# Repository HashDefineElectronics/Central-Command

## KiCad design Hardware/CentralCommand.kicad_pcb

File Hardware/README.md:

# Central-Command
The centralized board that will control the roll with it project

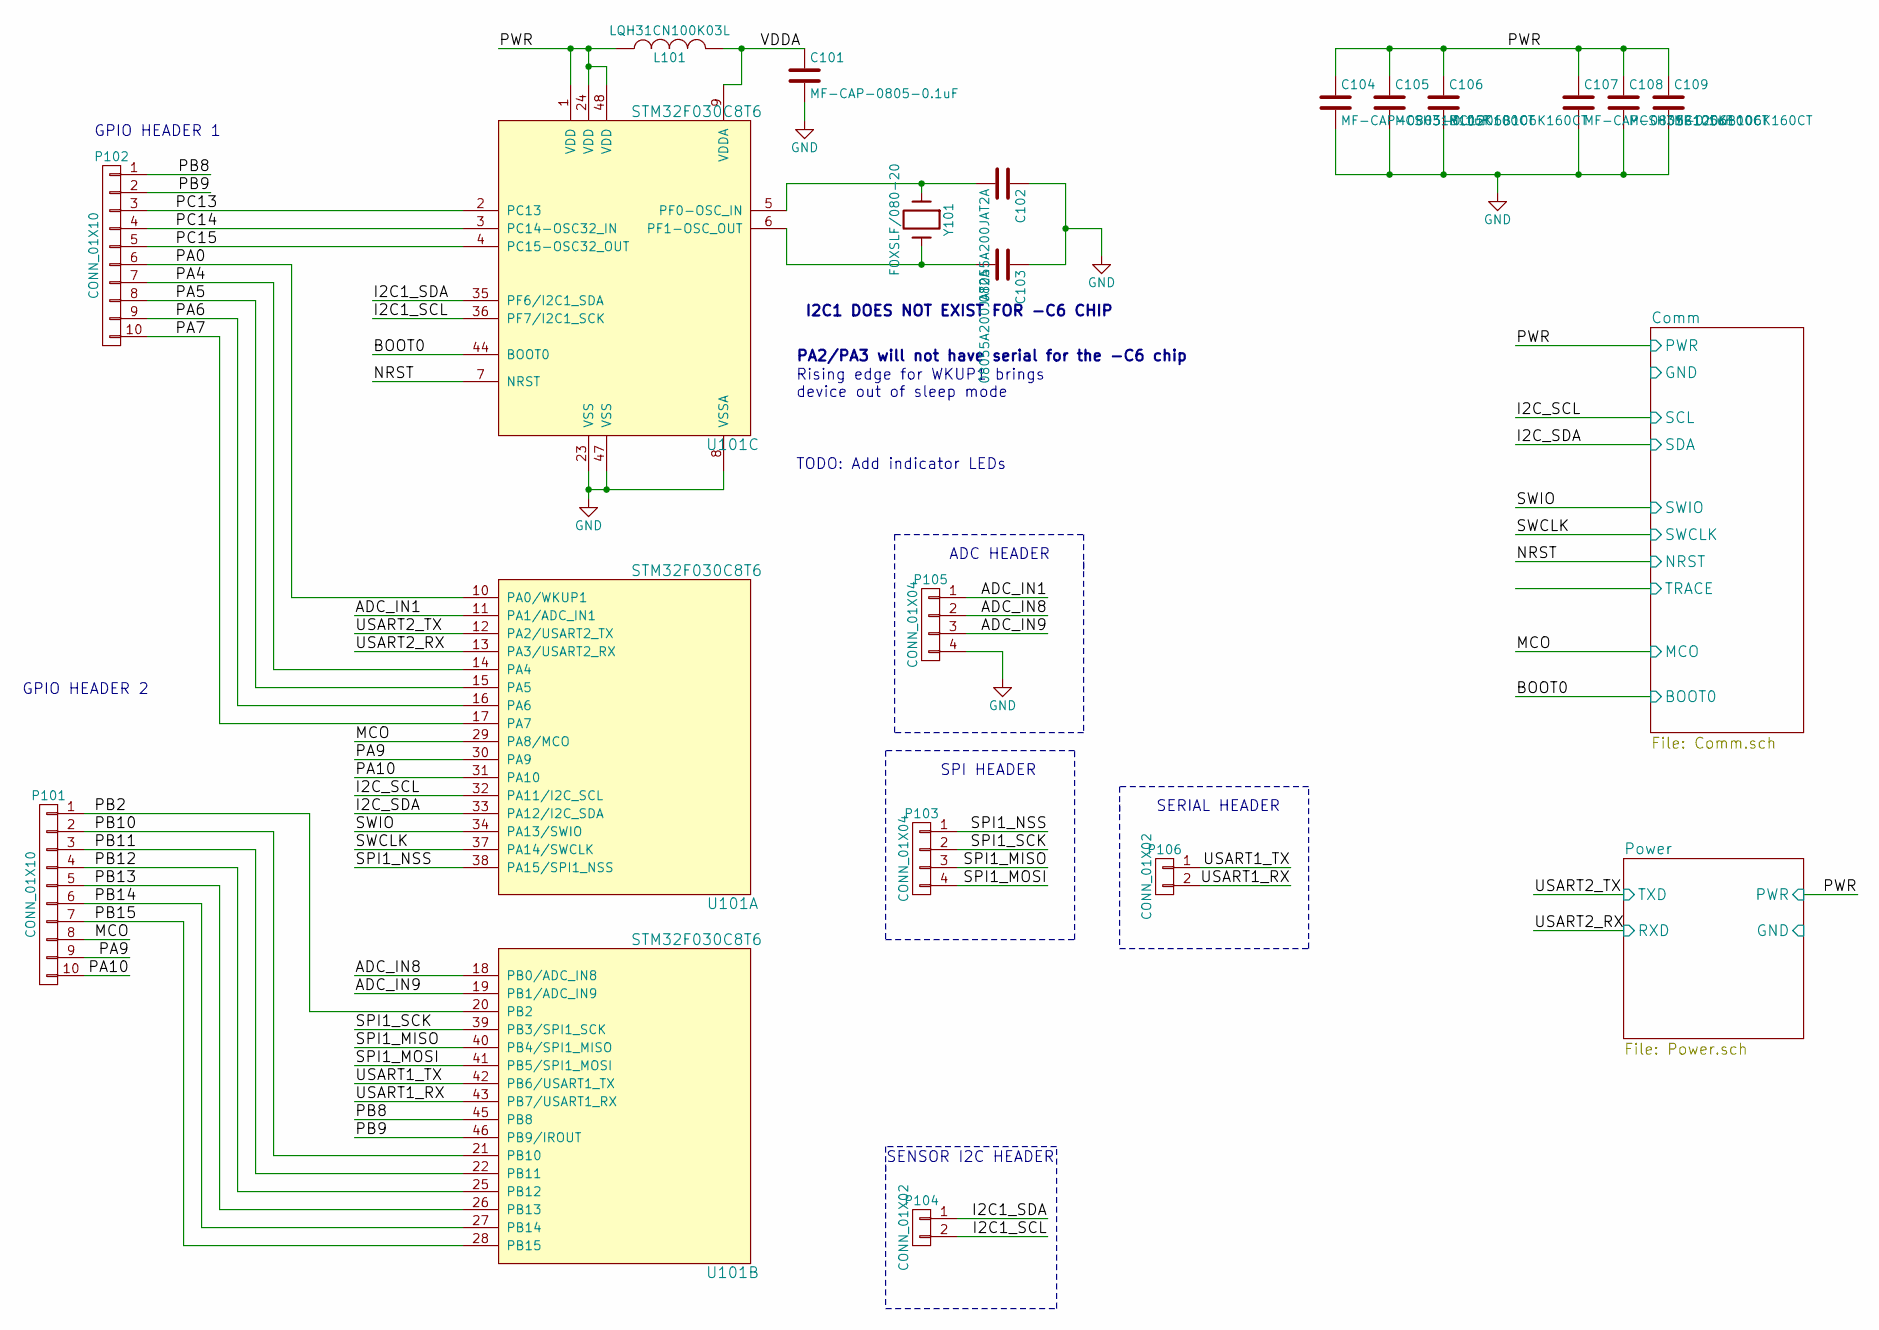
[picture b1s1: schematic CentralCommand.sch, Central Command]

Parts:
C101, C104, C107: MF-CAP-0805-0.1uF; C_0805; MPN 0805B104K500CT; Farnell 2496944
C102, C103: 08055A200JAT2A; C_0805; MPN 08055A200JAT2A; Farnell 2332762
C105, C108: MCSH31B105K100CT; C_1206; MPN MCSH31B105K100CT; Farnell 1856632
C106, C109: MC1206B106K160CT; C_1206; MPN MC1206B106K160CT; Farnell 2320921
L101: LQH31CN100K03L; Neosid_Inductor_SM1206; MPN LQH31CN100K03L; Farnell 1515399
P101, P102: CONN_01X10; Pin_Header_Straight_1x10; MPN M20-9991046; Farnell 1022261
P103, P105: CONN_01X04; Pin_Header_Straight_1x04; MPN M20-9990446; Farnell 1022251
P104, P106: CONN_01X02; Pin_Header_Straight_1x02; MPN M20-9990246; Farnell 1022247
U101: STM32F030C8T6; LQFP-48_7x7mm_Pitch0.5mm; MPN STM32F030C8; Farnell 2393634
Y101: FOXSLF/080-20; Crystal_HC49-U_Vertical; MPN FOXSLF/080-20; Farnell 2063945

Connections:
/ADC_IN1: P105.1, U101.11 (PA1/ADC_IN1)
/ADC_IN8: P105.2, U101.18 (PB0/ADC_IN8)
/ADC_IN9: P105.3, U101.19 (PB1/ADC_IN9)
/Comm/BOOT0: U101.44 (BOOT0); also elsewhere on the board
/Comm/NRST: U101.7 (NRST); also elsewhere on the board
/Comm/PWR: C104.1, C105.1, C106.1, C107.1, C108.1, C109.1, L101.1, U101.1 (VDD), U101.24 (VDD), U101.48 (VDD); also elsewhere on the board
/Comm/SCL: U101.32 (PA11/I2C_SCL); also elsewhere on the board
/Comm/SDA: U101.33 (PA12/I2C_SDA); also elsewhere on the board
/Comm/SWCLK: U101.37 (PA14/SWCLK); also elsewhere on the board
/Comm/SWIO: U101.34 (PA13/SWIO); also elsewhere on the board
/I2C1_SCL: P104.2, U101.36 (PF7/I2C1_SCK)
/I2C1_SDA: P104.1, U101.35 (PF6/I2C1_SDA)
/MCO: P101.8, U101.29 (PA8/MCO)
/PA0: P102.6, U101.10 (PA0/WKUP1)
/PA4: P102.7, U101.14 (PA4)
/PA5: P102.8, U101.15 (PA5)
/PA6: P102.9, U101.16 (PA6)
/PA7: P102.10, U101.17 (PA7)
/PA9: P101.9, U101.30 (PA9)
/PA10: P101.10, U101.31 (PA10)
/PB2: P101.1, U101.20 (PB2)
/PB8: P102.1, U101.45 (PB8)
/PB9: P102.2, U101.46 (PB9/IROUT)
/PB10: P101.2, U101.21 (PB10)
/PB11: P101.3, U101.22 (PB11)
/PB12: P101.4, U101.25 (PB12)
/PB13: P101.5, U101.26 (PB13)
/PB14: P101.6, U101.27 (PB14)
/PB15: P101.7, U101.28 (PB15)
/PC13: P102.3, U101.2 (PC13)
/PC14: P102.4, U101.3 (PC14-OSC32_IN)
/PC15: P102.5, U101.4 (PC15-OSC32_OUT)
/Power/RXD: U101.13 (PA3/USART2_RX); also elsewhere on the board
/Power/TXD: U101.12 (PA2/USART2_TX); also elsewhere on the board
/SPI1_MISO: P103.3, U101.40 (PB4/SPI1_MISO)
/SPI1_MOSI: P103.4, U101.41 (PB5/SPI1_MOSI)
/SPI1_NSS: P103.1, U101.38 (PA15/SPI1_NSS)
/SPI1_SCK: P103.2, U101.39 (PB3/SPI1_SCK)
/USART1_RX: P106.2, U101.43 (PB7/USART1_RX)
/USART1_TX: P106.1, U101.42 (PB6/USART1_TX)
/VDDA: C101.1, L101.2, U101.9 (VDDA)
GND: C101.2, C102.1, C103.1, C104.2, C105.2, C106.2, C107.2, C108.2, C109.2, P105.4, U101.8 (VSSA), U101.23 (VSS), U101.47 (VSS); also elsewhere on the board
unnamed: C102.2, U101.5 (PF0-OSC_IN), Y101.1
unnamed: C103.2, U101.6 (PF1-OSC_OUT), Y101.2

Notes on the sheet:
I2C1 DOES NOT EXIST FOR -C6 CHIP
PA2/PA3 will not have serial for the -C6 chip
Rising edge for WKUP1 brings device out of sleep mode
GPIO HEADER 1
ADC HEADER
SPI HEADER
SERIAL HEADER
SENSOR I2C HEADER
GPIO HEADER 2
TODO: Add indicator LEDs

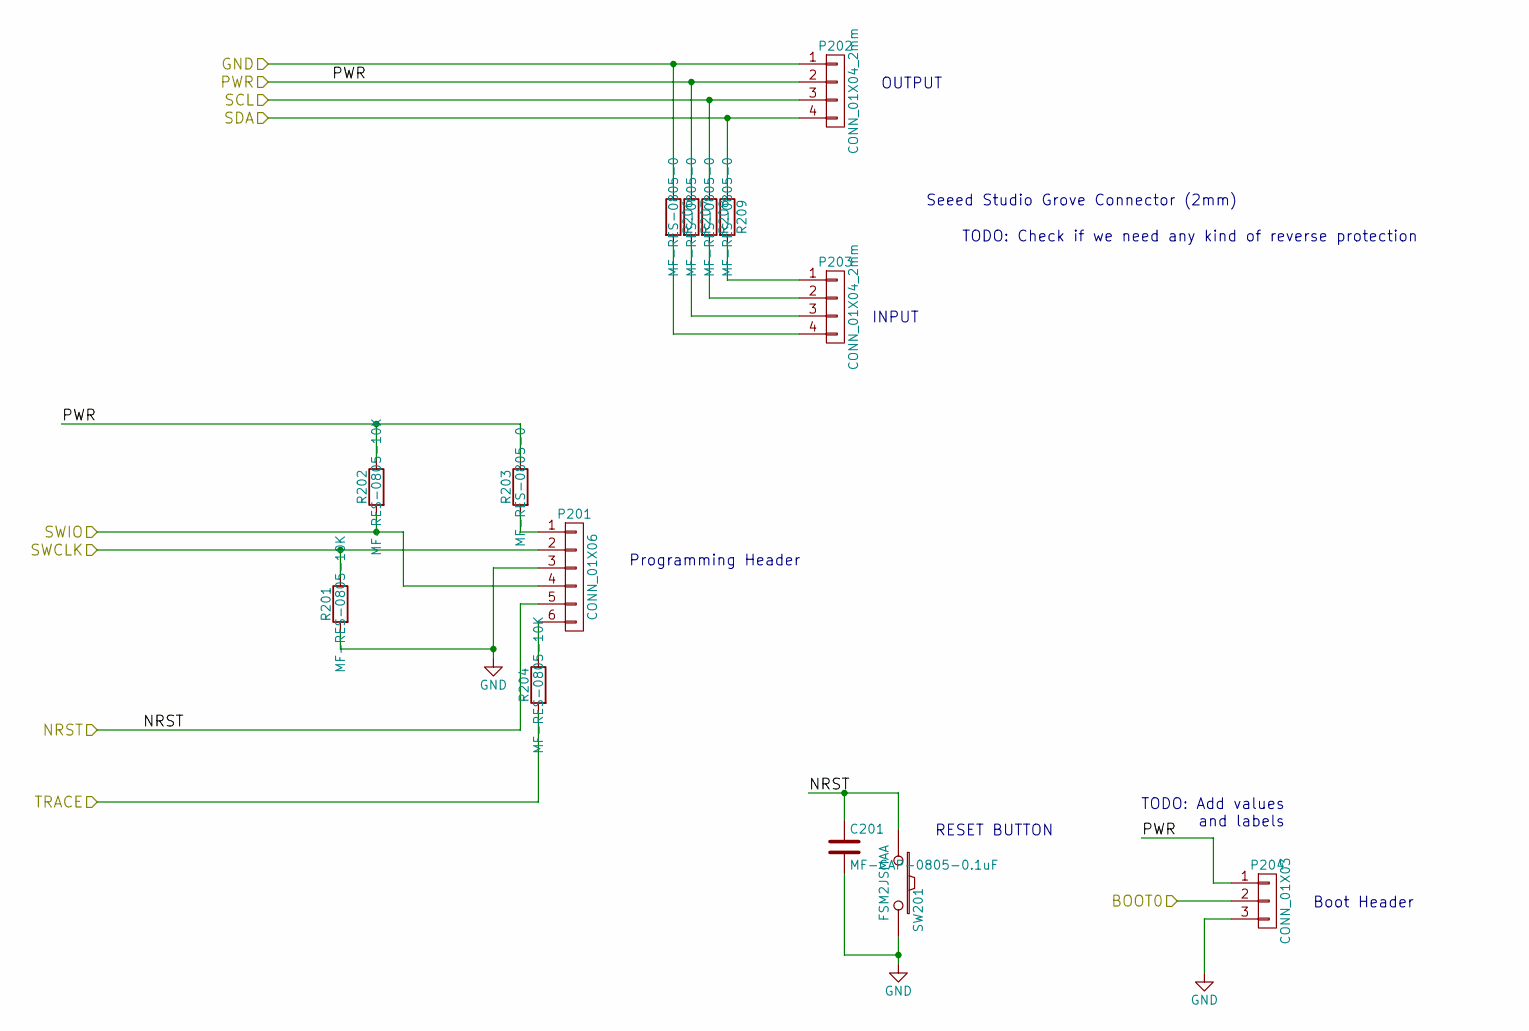
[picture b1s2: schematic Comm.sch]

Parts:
C201: MF-CAP-0805-0.1uF; C_0805; MPN 0805B104K500CT; Farnell 2496944
P201: CONN_01X06; Pin_Header_Straight_1x06; MPN M20-9990646; Farnell 1022255
P202, P203: CONN_01X04_2mm; Grove-2mm; MPN M22-2510405; Farnell 2289778
P204: CONN_01X03; Pin_Header_Straight_1x03; MPN M20-9990346; Farnell 1022249
R201, R202, R204: MF-RES-0805-10K; R_0805; MPN MCWR08X1002FTL; Farnell 2447553
R203, R206, R207, R208, R209: MF-RES-0805-0; R_0805; MPN MC01W08050R; Farnell 9333681
SW201: FSM2JSMAA; FSM2JSMAA-ND; MPN FSM2JSMAA; Farnell 2468760

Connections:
/Comm/BOOT0: P204.2; also elsewhere on the board
/Comm/NRST: C201.1, P201.5, SW201.1; also elsewhere on the board
/Comm/PWR: P202.2, P204.1, R202.1, R203.1, R207.1; also elsewhere on the board
/Comm/SCL: P202.3, R208.1; also elsewhere on the board
/Comm/SDA: P202.4, R209.1; also elsewhere on the board
/Comm/SWCLK: P201.2, R201.1; also elsewhere on the board
/Comm/SWIO: P201.4, R202.2; also elsewhere on the board
/Comm/TRACE: R204.2
GND: C201.2, P201.3, P202.1, P204.3, R201.2, R206.1, SW201.2; also elsewhere on the board
unnamed: P201.1, R203.2
unnamed: P201.6, R204.1
unnamed: P203.1, R209.2
unnamed: P203.2, R208.2
unnamed: P203.3, R207.2
unnamed: P203.4, R206.2

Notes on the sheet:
Seeed Studio Grove Connector (2mm)
TODO: Check if we need any kind of reverse protection
Programming Header
RESET BUTTON
TODO: Add values and labels
Boot Header
OUTPUT
INPUT

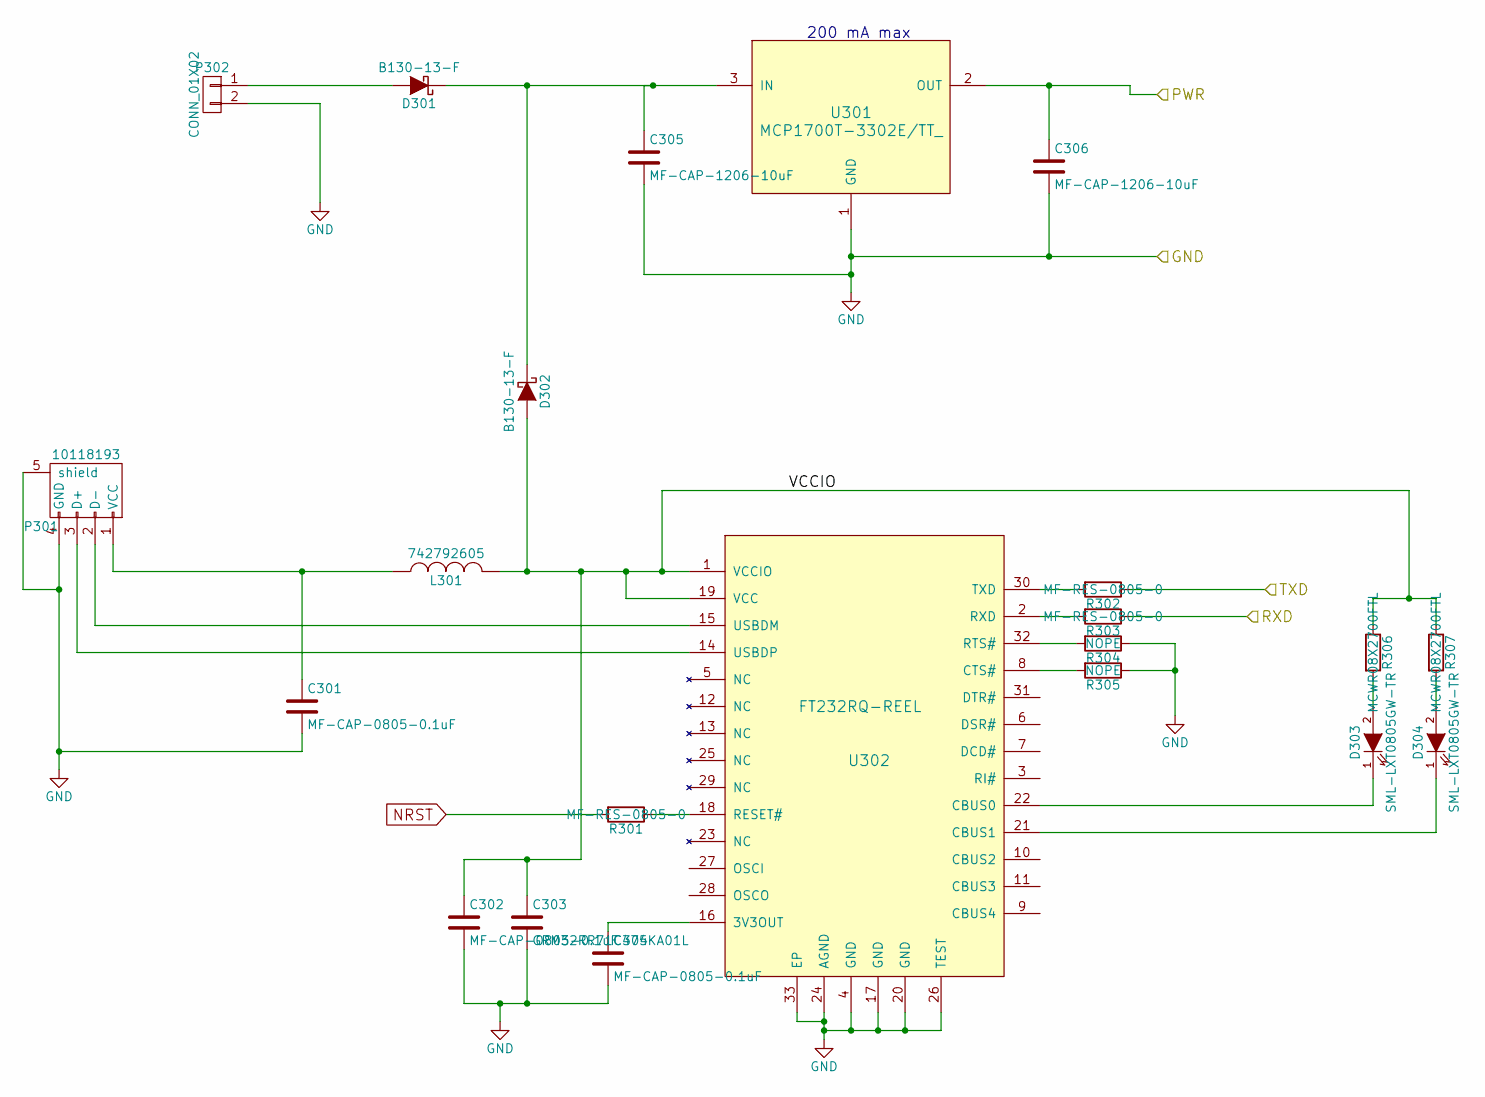
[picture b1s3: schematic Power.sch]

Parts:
C301, C302, C304: MF-CAP-0805-0.1uF; C_0805; MPN 0805B104K500CT; Farnell 2496944
C303: GRM32RR71C475KA01L; C_1210; MPN GRM32RR71C475KA01L; Farnell 1845775
C305: MF-CAP-1206-10uF; C_1210; MPN C1210C106Z4VACTU; Farnell 9227989
C306: MF-CAP-1206-10uF; C_1210; Farnell 9227989
D301, D302: B130-13-F; Diode-SMA_Standard; MPN B130-13-F; Farnell 1843713
D303, D304: SML-LXT0805GW-TR; LED-0805; MPN SML-LXT0805GW-TR; Farnell 2062259
L301: 742792605; Neosid_Inductor_SM1206; MPN 742792605; Farnell 1800342
P301: 10118193; MPN 10118193 or USB3075-30-A; Digi-Key 609-4616-1-ND
P302: CONN_01X02; Pin_Header_Straight_1x02; MPN M20-9990246; Farnell 1022247
R301, R302, R303: MF-RES-0805-0; R_0805; MPN MC01W08050R; Farnell 9333681
R304, R305: NOPE; R_0805
R306, R307: MCWR08X2700FTL; R_0805; MPN MCWR08X2700FTL; Farnell 2447618
U301: MCP1700T-3302E/TT_; SOT-23; MPN MCP1700T-3302E/TT_; Farnell 1296592
U302: FT232RQ-REEL; QFN-32-1EP_5x5mm_Pitch0.5mm; MPN FT232RQ-REEL; Farnell 1146033

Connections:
/Comm/PWR: C306.1, U301.2 (OUT); also elsewhere on the board
/Power/RXD: R303.1; also elsewhere on the board
/Power/TXD: R302.1; also elsewhere on the board
/Power/VCCIO: C302.1, C303.1, D302.2 (A), L301.2, R306.1, R307.1, U302.1 (VCCIO), U302.19 (VCC)
GND: C301.2, C302.2, C303.2, C304.2, C305.2, C306.2, P301.4 (GND), P301.5 (shield), P302.2, R304.1, R305.1, U301.1 (GND), U302.4 (GND), U302.17 (GND), U302.20 (GND), U302.24 (AGND), U302.26 (TEST), U302.33 (EP); also elsewhere on the board
NRST: R301.2
unnamed: C301.1, L301.1, P301.1 (VCC)
unnamed: C304.1, U302.16 (3V3OUT)
unnamed: C305.1, D301.1 (K), D302.1 (K), U301.3 (IN)
unnamed: D301.2 (A), P302.1
unnamed: D303.1 (K), U302.22 (CBUS0)
unnamed: D303.2 (A), R306.2
unnamed: D304.1 (K), U302.21 (CBUS1)
unnamed: D304.2 (A), R307.2
unnamed: P301.2 (D-), U302.15 (USBDM)
unnamed: P301.3 (D+), U302.14 (USBDP)
unnamed: R301.1, U302.18 (RESET#)
unnamed: R302.2, U302.30 (TXD)
unnamed: R303.2, U302.2 (RXD)
unnamed: R304.2, U302.32 (RTS#)
unnamed: R305.2, U302.8 (CTS#)

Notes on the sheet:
200 mA max

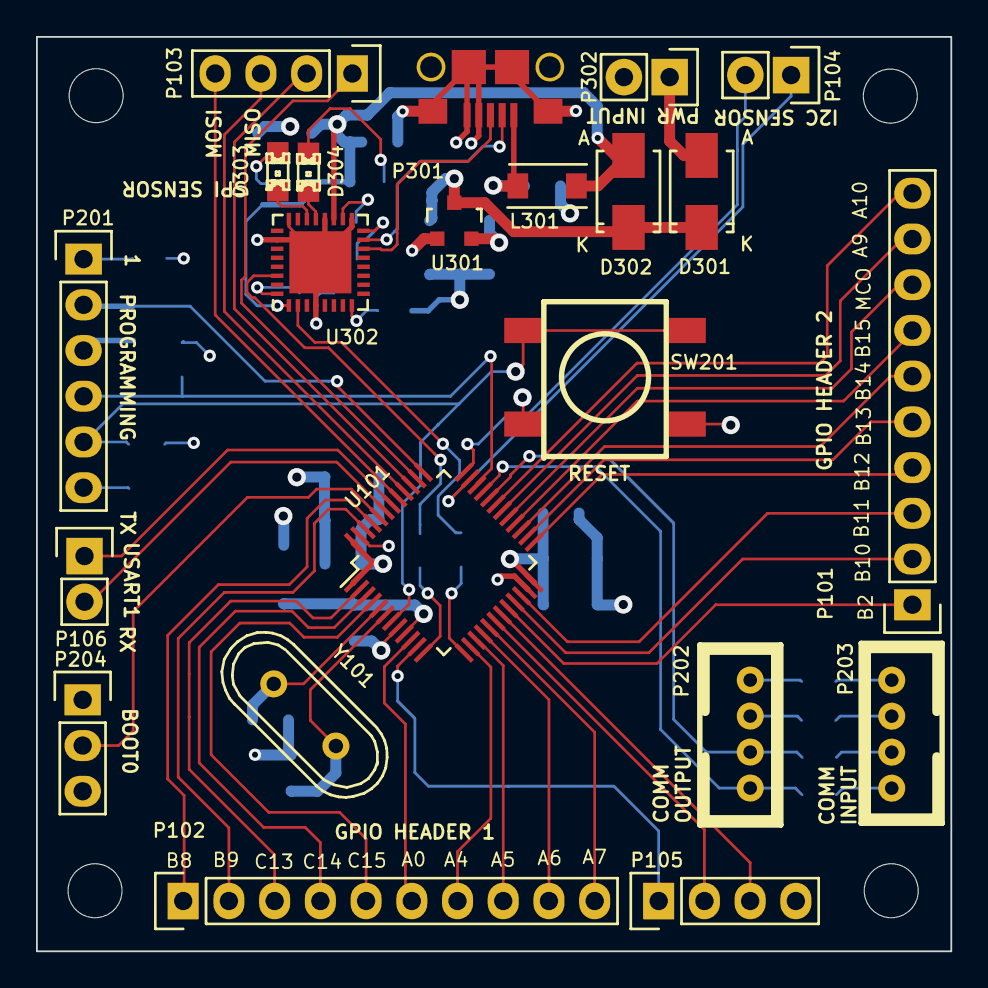
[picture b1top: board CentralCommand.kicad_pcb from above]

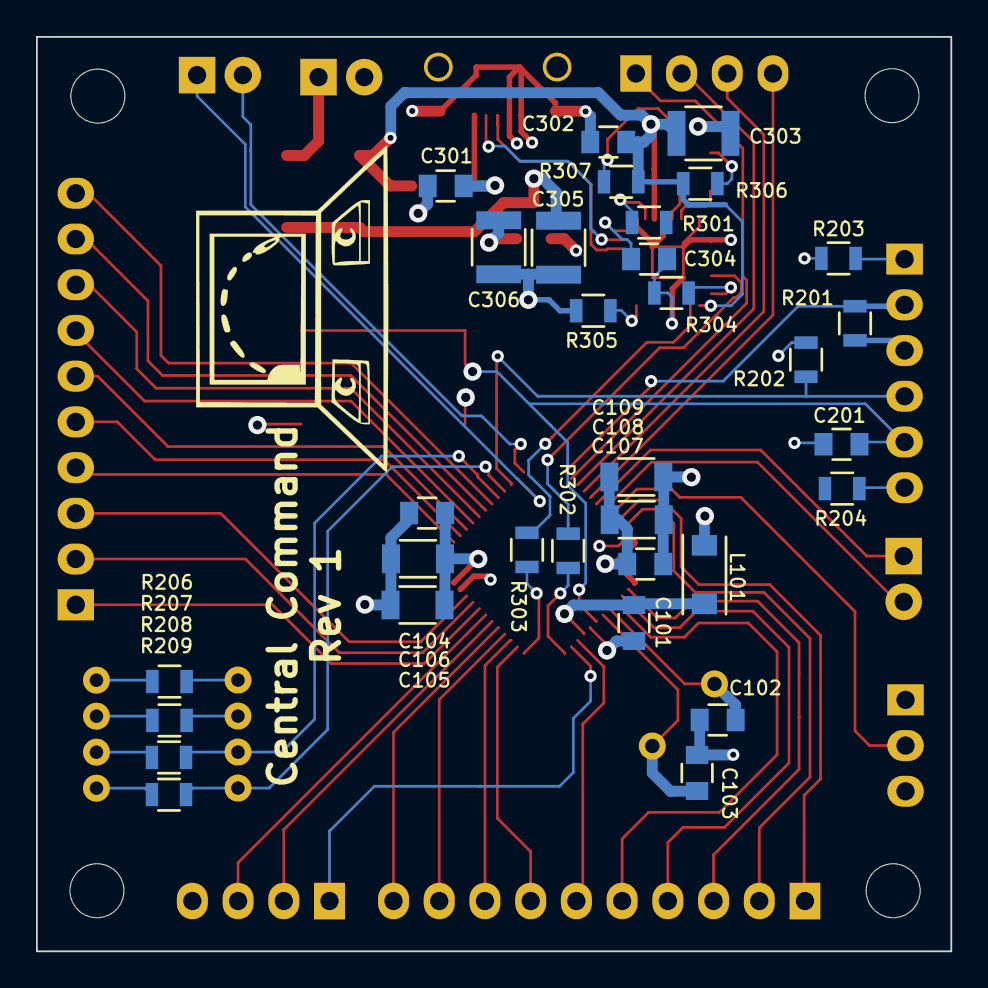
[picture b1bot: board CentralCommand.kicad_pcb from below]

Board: 4 copper layers, 50.8 x 50.8 mm, 54 parts (32 on the bottom side), 66 nets.

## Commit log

2015-10-11 New schematic
2015-10-11 Added initial STM32 footprint
2015-10-13 Finished assigning pins to the 3 banks of the symbol
2015-10-21 Added footprint for 3.3V fixed linear regulator and associated circuitry
2015-10-25 Updated pinout names and added programming headers
2015-10-27 Added ADC pins to STM32 symbol
2015-11-20 Changed out schematic symbol to match schematic in CC11 video. Should have been saved last time.
2015-11-20 Created layout, imported main 48 pin QFP
2015-11-23 Added Crystal to the schematic and layout
2015-11-23 Changed BOOT0 pin hookup, added reset button
2015-11-25 Added a USB to serial section
2015-11-25 Added more decoupling caps, indicator LEDs and hooked reset into the FTDI chip
2015-12-02 Added headers and created a new sheet for communication headers
2015-12-08 Associated footprints, created footprints for 2mm connector and did prelim placement
2015-12-09 Small changes after last large save
2015-12-09 Changed board outline (now 2x2) and placed headers around the outside based on pin connections.
2015-12-10 Swapped connections on the Grove connector
2015-12-22 Added ground and power layers.
2015-12-22 Added mounting holes (again?)
2015-12-22 Finished laying out power section
2015-12-23 Ripped up previous power layout and placed all FTDI components (finished page 3 of schematic)
2015-12-26 Swapped two connectors and routed the bottom connector
2015-12-26 Removed one header and finished connecting all parts
2015-12-26 Finished layout including labels and DRC
2016-01-05 Finished board and generated gerbers
2016-01-14 - Added Documentation folder - Move cad files to the hardware folder - generated the html BOM
2016-01-19 Rename project files to remove the space between 'Central' & 'Command' for the XSL processing of the BOM
2016-01-27 - Added Farnell and digi-key supplier numbers to most past. Still need todo crystal, switch and micro inductor. - updated the HTML BOM and CSV
2016-01-27 Added the farnell code for the last few parts
2016-01-27 minor farnell number correction
2016-01-28 Fixed the seed studion connect farnell code. It now points to the 2mm version
2016-02-01 Added the programming cable documentation and images
2016-02-01 Converted specs to Markdown
2016-02-03 XML file from creating BOM
2016-02-03 Removed Ron's Farnell files for this branch
2016-02-08 Updated for macrofab gerber names
2016-02-08 Tested changing value to the MPN
2016-02-08 Changed the component values to hold MPNs for Macrofab processing
2016-02-08 Updated layout file, as that's what we're submitting to MF
2016-02-10 - added eclipse test project - added stm32 datasheet
2016-02-11 The boardtest project will now enable the MCO so that we can meassure the system internal clock.
2016-02-22 Ported the serial iterface code from the embedded
2016-07-29 - Added the CE official KiCad Libary as a submodule. - also adde the gitignore to the main kicad project file.
2016-09-28 Added the changes made to the KiCad libs
2016-09-28 updated the CE_KiCadLib libary and update the Project library ref
2016-10-12 added and updated the project libary
2019-04-29 Ported the central-command firmware to platformio
